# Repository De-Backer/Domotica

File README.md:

# Domotica
head, contains AVR and PC  (Linux / SUSE) software  
*  [wiki](https://github.com/De-Backer/Domotica/wiki)  
*  [www](http://de-backer.github.io/Domotica)  
opm.:  
--Server:  
  start from Server.pro  
--AVR:  
  to build use makefile (QT build does not work).

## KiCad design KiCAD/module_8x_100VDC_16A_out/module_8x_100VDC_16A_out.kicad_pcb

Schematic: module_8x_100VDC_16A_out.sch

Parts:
D1, D2, D3, D4, D5, D6, D7, D8: LED; LED_D3.0mm_Clear
D9: 9V1; D_DO-35_SOD27_P7.62mm_Horizontal
J1: Conn_01x10_Male; JST_XH_B10B-XH-A_1x10_P2.50mm_Vertical
J2: Conn_01x09_Male; PhoenixContact_MSTBVA_2,5_9-G-5,08_1x09_P5.08mm_Vertical
Q1, Q2, Q4, Q5, Q6, Q8: IRF540N; TO-220-3_Horizontal_TabDown
Q3, Q7: IRF540N; TO-220-3_Horizontal_TabUp_no_hole
R1, R2, R3, R4, R5, R6, R7, R8: 330R; R_Axial_DIN0204_L3.6mm_D1.6mm_P5.08mm_Horizontal
R9, R10, R11, R12, R13, R14, R15, R16, R17: R; R_Axial_DIN0204_L3.6mm_D1.6mm_P5.08mm_Horizontal
U1, U2: PC847; DIP-16_W7.62mm_LongPads

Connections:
/+9V: D9.1, R9.2, U1.1, U1.3, U1.5, U1.7, U2.1, U2.3, U2.5, U2.7
/+24V: J1.10, R9.1
/GNDD: D1.1, D2.1, D3.1, D4.1, D5.1, D6.1, D7.1, D8.1, J1.1
/GPB0: J1.2, R1.1
/GPB1: J1.3, R2.1
/GPB2: J1.4, R3.1
/GPB3: J1.5, R4.1
/GPB4: J1.6, R5.1
/GPB5: J1.7, R6.1
/GPB6: J1.8, R7.1
/GPB7: J1.9, R8.1
/PWR_GND: D9.2, J2.9, Q1.3 (S), Q2.3 (S), Q3.3 (S), Q4.3 (S), Q5.3 (S), Q6.3 (S), Q7.3 (S), Q8.3 (S), R10.2, R11.2, R12.2, R13.2, R14.2, R15.2, R16.2, R17.2
/out0: J2.1, Q1.2 (D)
/out1: J2.2, Q2.2 (D)
/out2: J2.3, Q3.2 (D)
/out3: J2.4, Q4.2 (D)
/out4: J2.5, Q5.2 (D)
/out5: J2.6, Q6.2 (D)
/out6: J2.7, Q7.2 (D)
/out7: J2.8, Q8.2 (D)
unnamed: D1.2, U1.15
unnamed: D2.2, U1.13
unnamed: D3.2, U1.11
unnamed: D4.2, U1.9
unnamed: D5.2, U2.15
unnamed: D6.2, U2.13
unnamed: D7.2, U2.11
unnamed: D8.2, U2.9
unnamed: Q1.1 (G), R10.1, U1.2
unnamed: Q2.1 (G), R11.1, U1.4
unnamed: Q3.1 (G), R12.1, U1.6
unnamed: Q4.1 (G), R13.1, U1.8
unnamed: Q5.1 (G), R14.1, U2.2
unnamed: Q6.1 (G), R15.1, U2.4
unnamed: Q7.1 (G), R16.1, U2.6
unnamed: Q8.1 (G), R17.1, U2.8
unnamed: R1.2, U1.16
unnamed: R2.2, U1.14
unnamed: R3.2, U1.12
unnamed: R4.2, U1.10
unnamed: R5.2, U2.16
unnamed: R6.2, U2.14
unnamed: R7.2, U2.12
unnamed: R8.2, U2.10

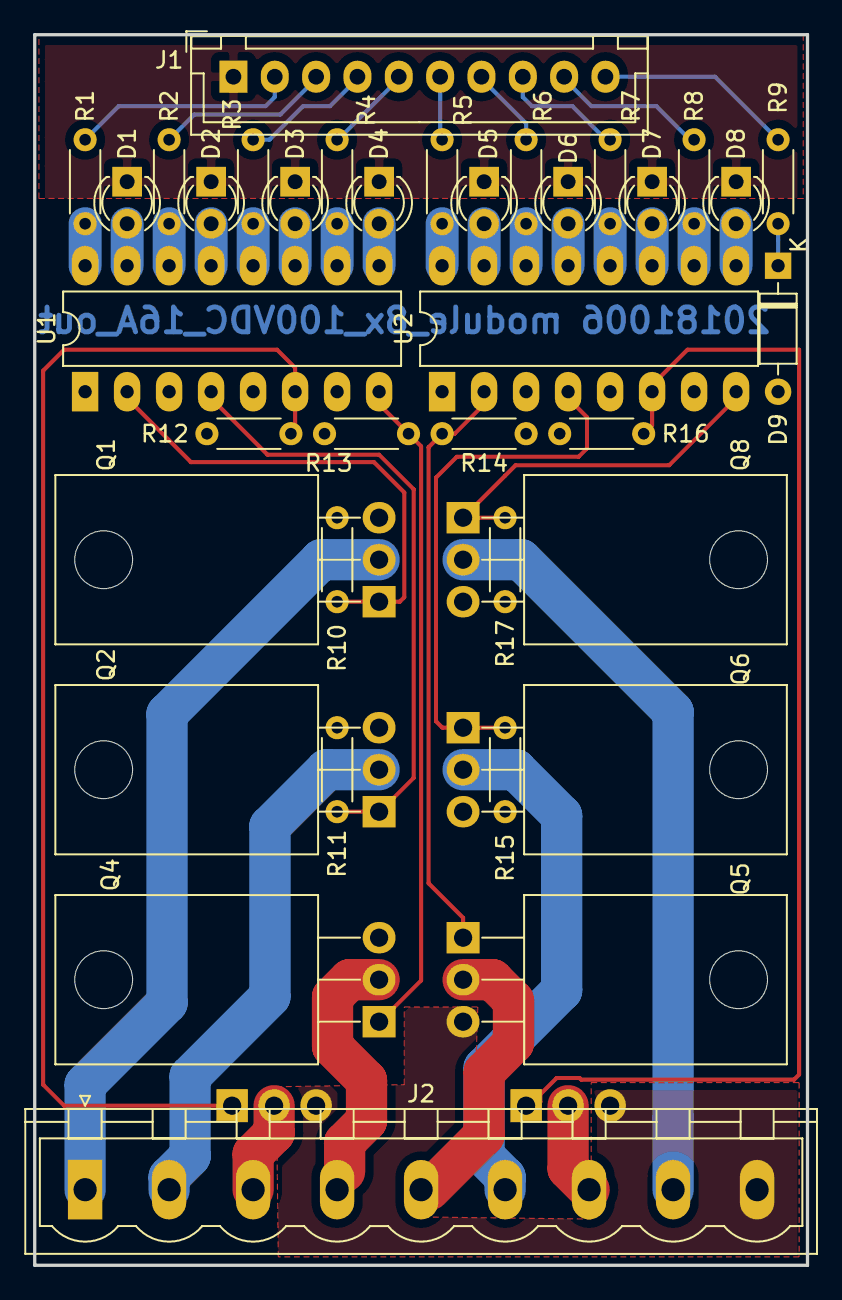
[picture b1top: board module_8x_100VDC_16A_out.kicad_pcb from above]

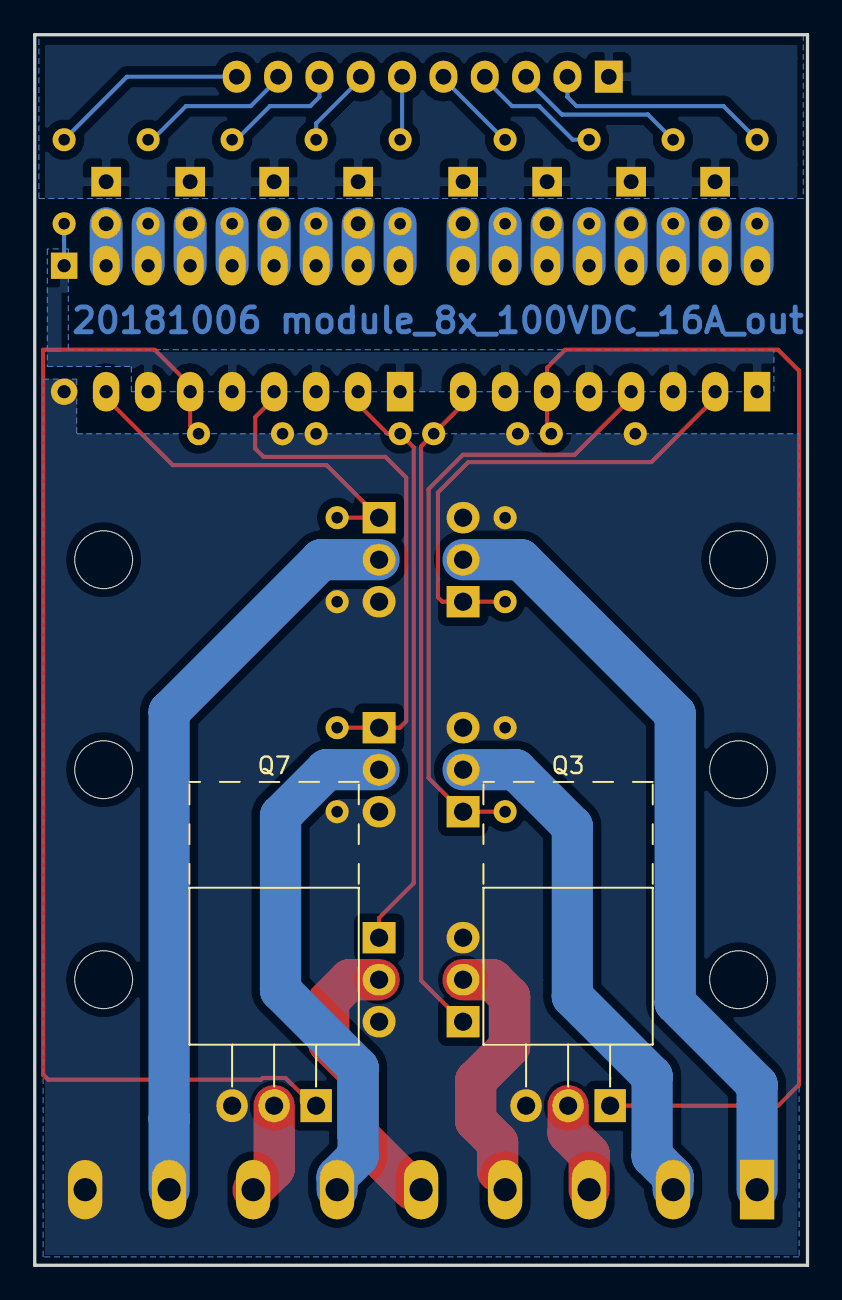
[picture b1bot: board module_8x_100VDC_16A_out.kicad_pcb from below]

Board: 2 copper layers, 46.7 x 74.4 mm, 38 parts (2 on the bottom side), 44 nets.

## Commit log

2015-01-10 ad *.pro files
2015-01-10 ad slave avr
2015-01-10 ad Master
2015-01-10 add server
2015-01-10 ad eagle
2015-01-10 Create gh-pages branch via GitHub
2015-01-11 modified master Branch to com_usb
2015-01-11 usb werkt nog protokols invoegen
2015-01-12 test
2015-01-13 ad images
2015-01-13 start van memory io
2015-01-14 ad io-data
2015-01-14 ad usb com
2015-01-17 ad debug fusie
2015-01-18 usb com Slave werkt
2018-10-18 add kicad print 8x 100VDC 16A Signed-off-by: Simon De Backer <simondebacker@msn.com>
2018-10-18 aad net list
2018-10-18 add gerber
2023-01-15 Add submodule domotica_AVR domotica_eeprom_app
